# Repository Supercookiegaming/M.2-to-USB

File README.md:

# M.2-to-USB Adapter Card

## Overview
The M.2 to USB adapater uses the single USB 2.0 lane on the A/E Key M.2 slot to make an USB 2.0 front panel connector. The board uses the Microchip USB2422 2 port USB 2.0 hub chipset.
## Specifications
1. 500mA per port
2. Short circuit protection
3. 2 USB 2.0 ports (combined into standard internal PC header)
4. 2230 A & E Key compatibility
## Instructions

* [Ordering Instructions](Instructions/PCB_Order_Instructions.md)
* [KiCad Instructions](Instructions/KiCad_Install_Instructions.md)
* [Soldering Instructions](Instructions/Soldering_Instructions.md)

The board is free to use for personal use only.

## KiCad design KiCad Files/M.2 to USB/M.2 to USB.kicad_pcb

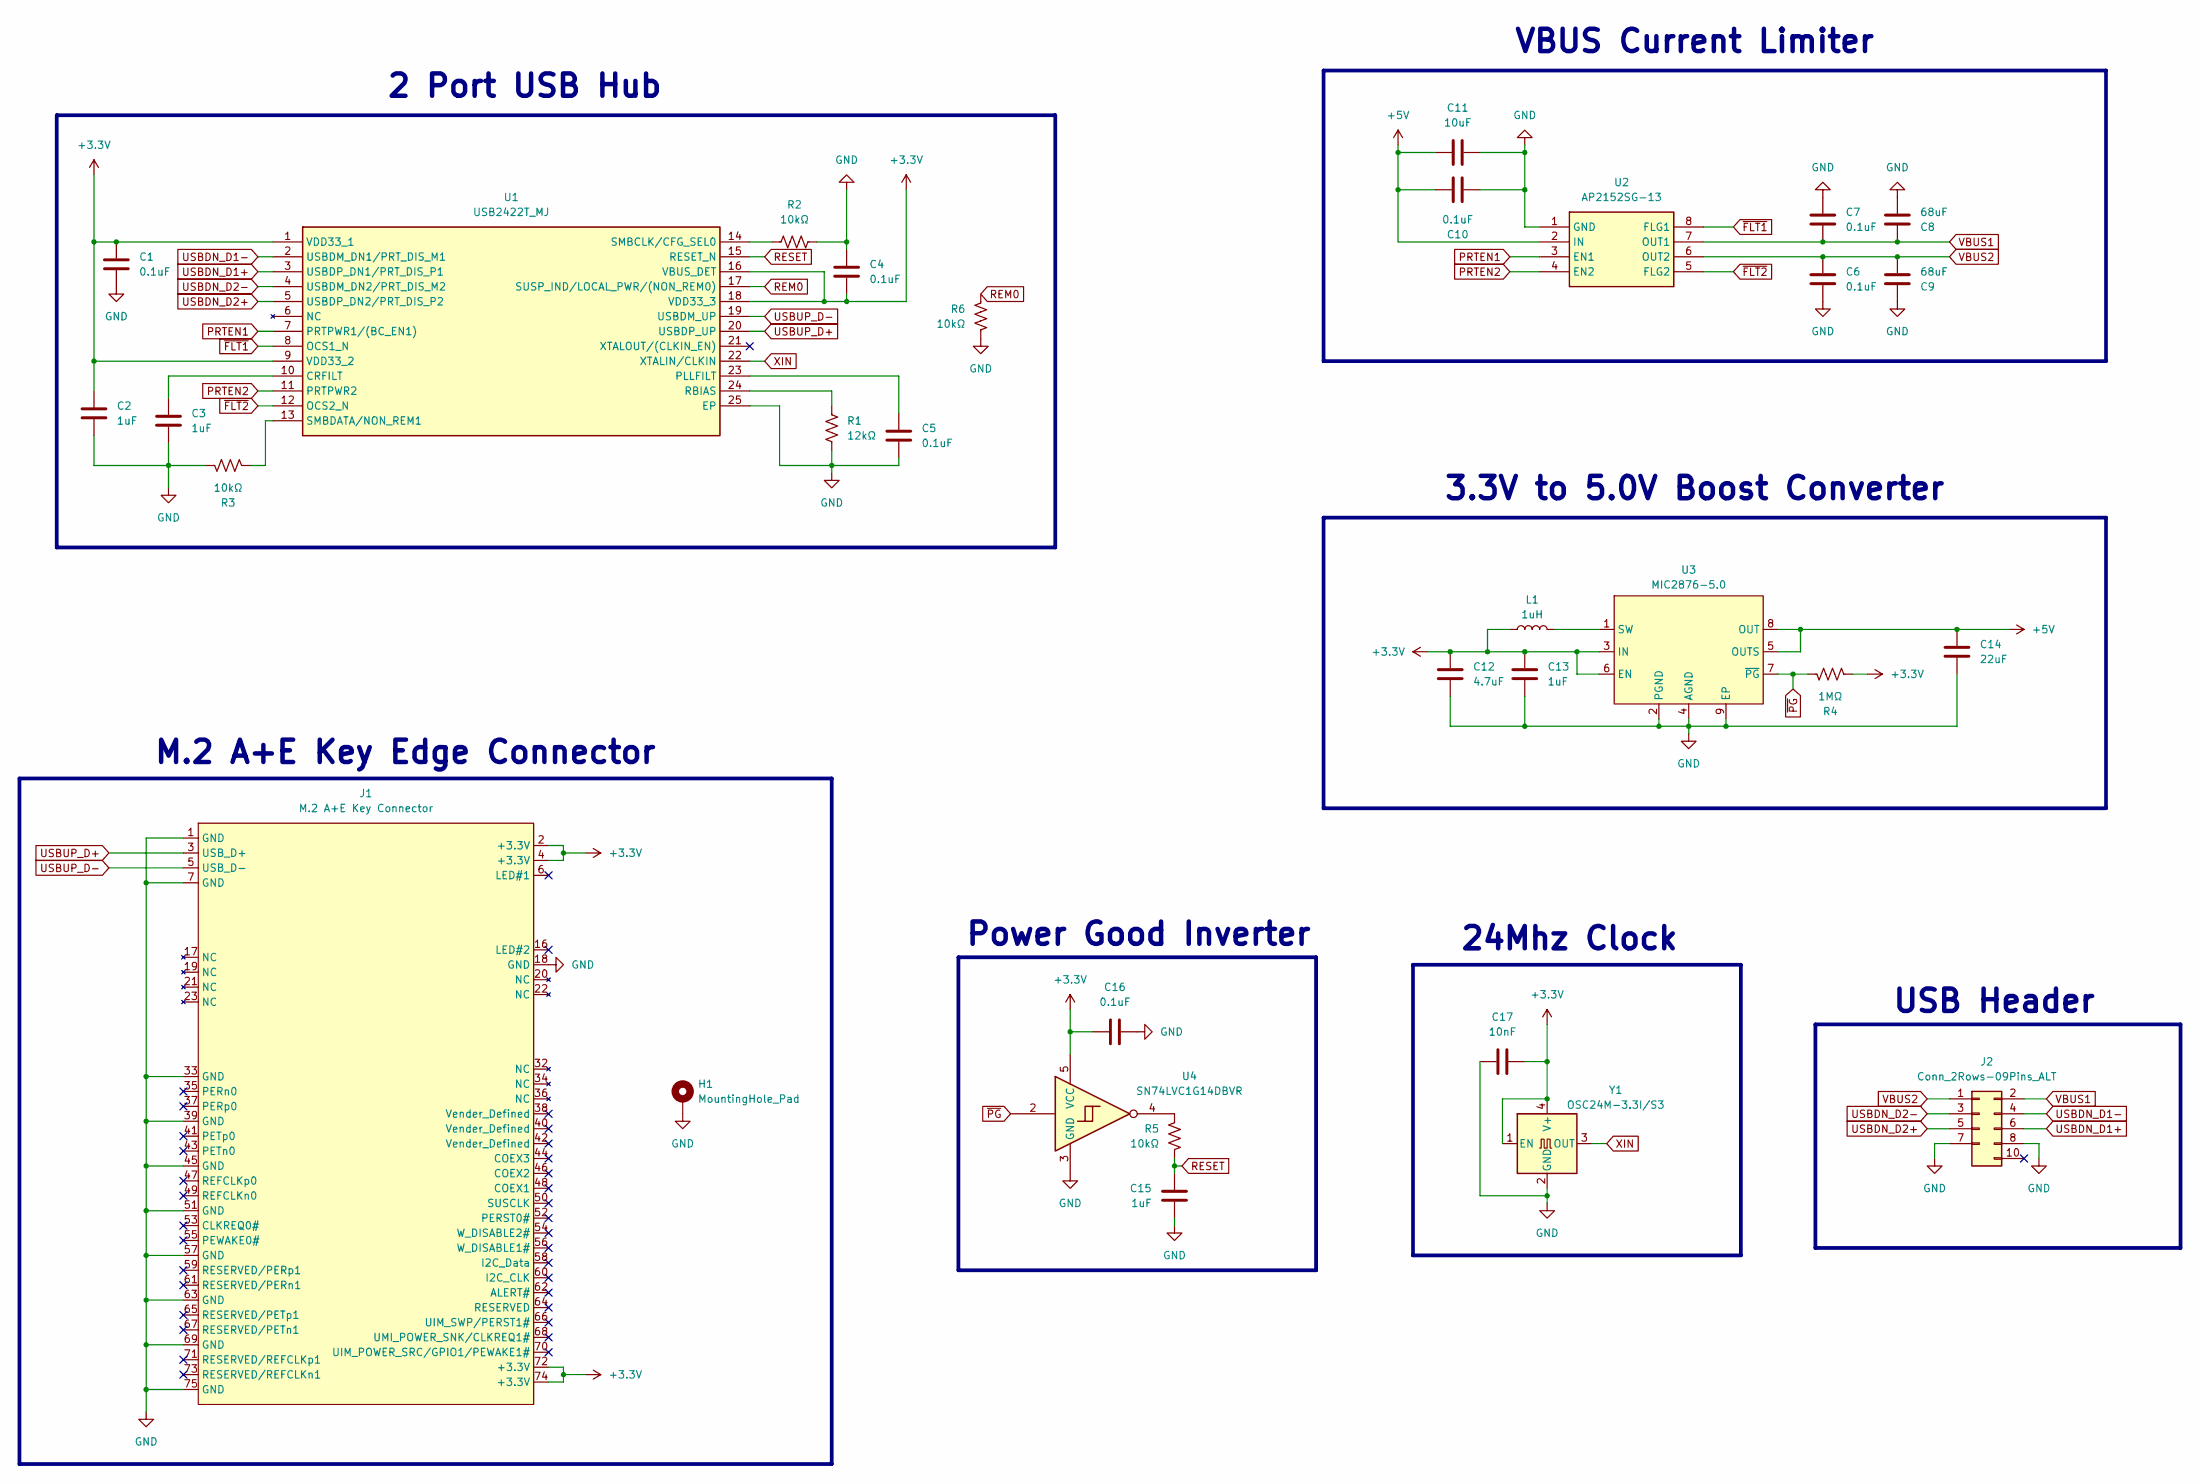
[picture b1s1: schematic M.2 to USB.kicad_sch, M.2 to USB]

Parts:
C1, C4, C5, C6, C7, C10, C16: 0.1uF; C_0402_1005Metric
C2, C3, C13, C15: 1uF; C_0402_1005Metric
C8, C9: 68uF; C_1206_3216Metric
C11: 10uF; C_0402_1005Metric
C12: 4.7uF; C_0402_1005Metric
C14: 22uF; C_0805_2012Metric
C17: 10nF; C_0402_1005Metric
H1: MountingHole_Pad; M.2 Mounting Pad
J1: M.2 A+E Key Connector
J2: Conn_2Rows-09Pins_ALT; PinHeader_2x05_P2.54mm_Vertical_KEY_9
L1: 1uH; L_2520_INPAQ
R1: 12kΩ; R_0402_1005Metric
R2, R3, R5, R6: 10kΩ; R_0402_1005Metric
R4: 1MΩ; R_0402_1005Metric
U1: USB2422T_MJ; QFN50P400X400X100-25N-D; Manufacturer_Part_Number USB2422T/MJ; Mouser Part Number 579-USB2422T/MJ
U2: AP2152SG-13; SOIC127P600X175-8N; Manufacturer_Part_Number AP2152SG-13; Mouser Part Number 621-AP2152SG-13
U3: MIC2876-5.0; 8-Lead UDFN
U4: SN74LVC1G14DBVR; SOT-23-5
Y1: OSC24M-3.3I/S3; 4-SMD-3.2-2.5

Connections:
+3.3V: C1.1, C2.1, C4.2, C12.1, C13.1, C16.1, C17.1, J1.2 (+3.3V), J1.4 (+3.3V), J1.72 (+3.3V), J1.74 (+3.3V), L1.1, R4.1, U1.1 (VDD33_1), U1.9 (VDD33_2), U1.16 (VBUS_DET), U1.18 (VDD33_3), U3.3 (IN), U3.6 (EN), U4.5 (VCC), Y1.1 (EN), Y1.4 (V+)
+5V: C10.1, C11.1, C14.1, U2.2 (IN), U3.5 (OUTS), U3.8 (OUT)
GND: C1.2, C2.2, C3.2, C4.1, C5.2, C6.2, C7.1, C8.2, C9.1, C10.2, C11.2, C12.2, C13.2, C14.2, C15.2, C16.2, C17.2, H1.1, J1.1 (GND), J1.7 (GND), J1.18 (GND), J1.33 (GND), J1.39 (GND), J1.45 (GND), J1.51 (GND), J1.57 (GND), J1.63 (GND), J1.69 (GND), J1.75 (GND), J2.7, J2.8, R1.2, R2.2, R3.2, R6.2, U1.25 (EP), U2.1 (GND), U3.2 (PGND), U3.4 (AGND), U3.9 (EP), U4.3 (GND), Y1.2 (GND)
unnamed: R5.1, U4.4
unnamed: C3.1, U1.10 (CRFILT)
unnamed: C5.1, U1.23 (PLLFILT)
unnamed: R1.1, U1.24 (RBIAS)
unnamed: R2.1, U1.14 (SMBCLK/CFG_SEL0)
unnamed: R3.1, U1.13 (SMBDATA/NON_REM1)
unnamed: L1.2, U3.1 (SW)
PRTEN1: U1.7 (PRTPWR1/(BC_EN1)), U2.3 (EN1)
PRTEN2: U1.11 (PRTPWR2), U2.4 (EN2)
REM0: R6.1, U1.17 (SUSP_IND/LOCAL_PWR/(NON_REM0))
RESET: C15.1, R5.2, U1.15 (RESET_N)
USBDN_D1+: J2.6, U1.3 (USBDP_DN1/PRT_DIS_P1)
USBDN_D1-: J2.4, U1.2 (USBDM_DN1/PRT_DIS_M1)
USBDN_D2+: J2.5, U1.5 (USBDP_DN2/PRT_DIS_P2)
USBDN_D2-: J2.3, U1.4 (USBDM_DN2/PRT_DIS_M2)
USBUP_D+: J1.3 (USB_D+), U1.20 (USBDP_UP)
USBUP_D-: J1.5 (USB_D-), U1.19 (USBDM_UP)
VBUS1: C7.2, C8.1, J2.2, U2.7 (OUT1)
VBUS2: C6.1, C9.2, J2.1, U2.6 (OUT2)
XIN: U1.22 (XTALIN/CLKIN), Y1.3 (OUT)
~FLT1: U1.8 (OCS1_N), U2.8 (FLG1)
~FLT2: U1.12 (OCS2_N), U2.5 (FLG2)
~PG: R4.2, U3.7 (~PG), U4.2

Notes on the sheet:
VBUS Current Limiter
2 Port USB Hub
M.2 A+E Key Edge Connector
Power Good Inverter
USB Header
3.3V to 5.0V Boost Converter
24Mhz Clock

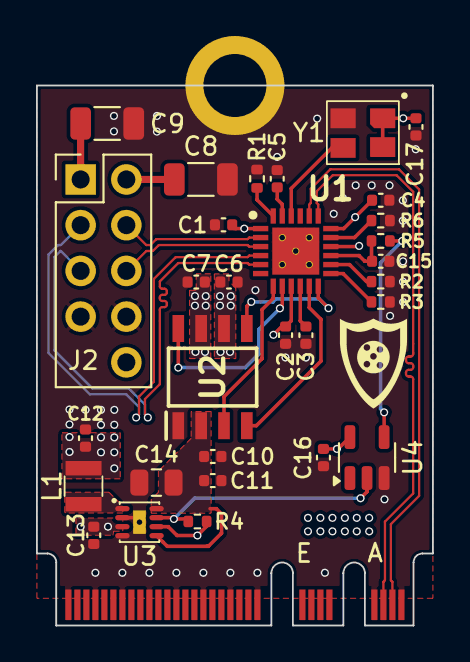
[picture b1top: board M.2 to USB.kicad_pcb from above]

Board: 4 copper layers, 22.0 x 30.0 mm, 32 parts (0 on the bottom side), 26 nets.

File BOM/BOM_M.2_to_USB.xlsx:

Board QTY | 1
Total Price | 8.0399999999999991
Board Designator | Part Number | Part Purpose | QTY per Board | Unit Price | QTY Needed | Total Price | Link
U1 | USB2422/MJ | USB Hub | 1 | 1.49 | 1 | 1.49 | https://www.digikey.com/en/products/detail/microchip-technol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
U2 | AP2152SG-13 | USB VBUS Current Limiter | 1 | 0.39 | 1 | 0.39 | https://www.digikey.com/en/products/detail/diodes-incorporat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
U3 | MIC2876-5.0YMT-TR | 5V Boost Converter | 1 | 0.62 | 1 | 0.62 | https://www.digikey.com/en/products/detail/microchip-technol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
U4 | SN74LVC1G14DBVR | PG Signal Inverter | 1 | 0.11 | 1 | 0.11 | https://www.digikey.com/en/products/detail/texas-instruments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
Y1 | OSC24M-3.3I/S3 | 24Mhz Clock Generator | 1 | 0.73 | 1 | 0.73 | https://www.digikey.com/en/products/detail/yic/OSC24M-3-3I-S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
J2 | HTSW-105-07-T-D-009 | Internal USB 2.0 Header | 1 | 0.96 | 1 | 0.96 | https://www.digikey.com/en/products/detail/samtec-inc/HTSW-1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
R1 | RC0402FR-0712KL | 12kΩ Bias Resistor | 1 | 0.1 | 1 | 0.1 | https://www.digikey.com/en/products/detail/yageo/RC0402FR-07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
R2, R3, R5, R6 | RC0402FR-0712KL | 10kΩ Pull Up/Down Resistor | 4 | 0.1 | 4 | 0.4 | https://www.digikey.com/en/products/detail/yageo/RC0402JR-07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
R4 | WR04X1004FTL | 1MΩ Power Good Pull Up Resistor | 1 | 0.1 | 1 | 0.1 | https://www.digikey.com/en/products/detail/walsin-technology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
C1, C4, C5, C6, C7, C10, C16 | CL05A104KP5NNNC | 0.1uF Decoupling Caps | 7 | 0.08 | 7 | 0.56000000000000005 | https://www.digikey.com/en/products/detail/samsung-electro-m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
C2, C3, C13, C15 | C0402C105K9PACTU | 1uF Decoupling Caps | 4 | 0.08 | 4 | 0.32 | https://www.digikey.com/en/products/detail/kemet/C0402C105K9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
C8, C9 | C3216X5R0J686M160AB | 68uF VBUS Bulk Capacitors | 2 | 0.89 | 2 | 1.78 | https://www.digikey.com/en/products/detail/tdk-corporation/C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
C11 | GRM155R61A106ME11D | 10uF Decoupling Cap | 1 | 0.08 | 1 | 0.08 | https://www.digikey.com/en/products/detail/murata-electronic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
C12 | CL05A475KQ5NRNC | 4.7uF Input Cap for Boost Regtulator | 1 | 0.08 | 1 | 0.08 | https://www.digikey.com/en/products/detail/samsung-electro-m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
C14 | CL21A226MQQNNNG | 22uF Output Cap for Boost Regulator | 1 | 0.12 | 1 | 0.12 | https://www.digikey.com/en/products/detail/samsung-electro-m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
C17 | 0402B103K6R3CT | 10nF Decoupling Cap for Clock Chip | 1 | 0.1 | 1 | 0.1 | https://www.digikey.com/en/products/detail/walsin-technology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
L1 | WIP252012S-1R0MLDG | 1uH Boost Converter Inductor | 1 | 0.1 | 1 | 0.1 | https://www.digikey.com/en/products/detail/inpaq-technology-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

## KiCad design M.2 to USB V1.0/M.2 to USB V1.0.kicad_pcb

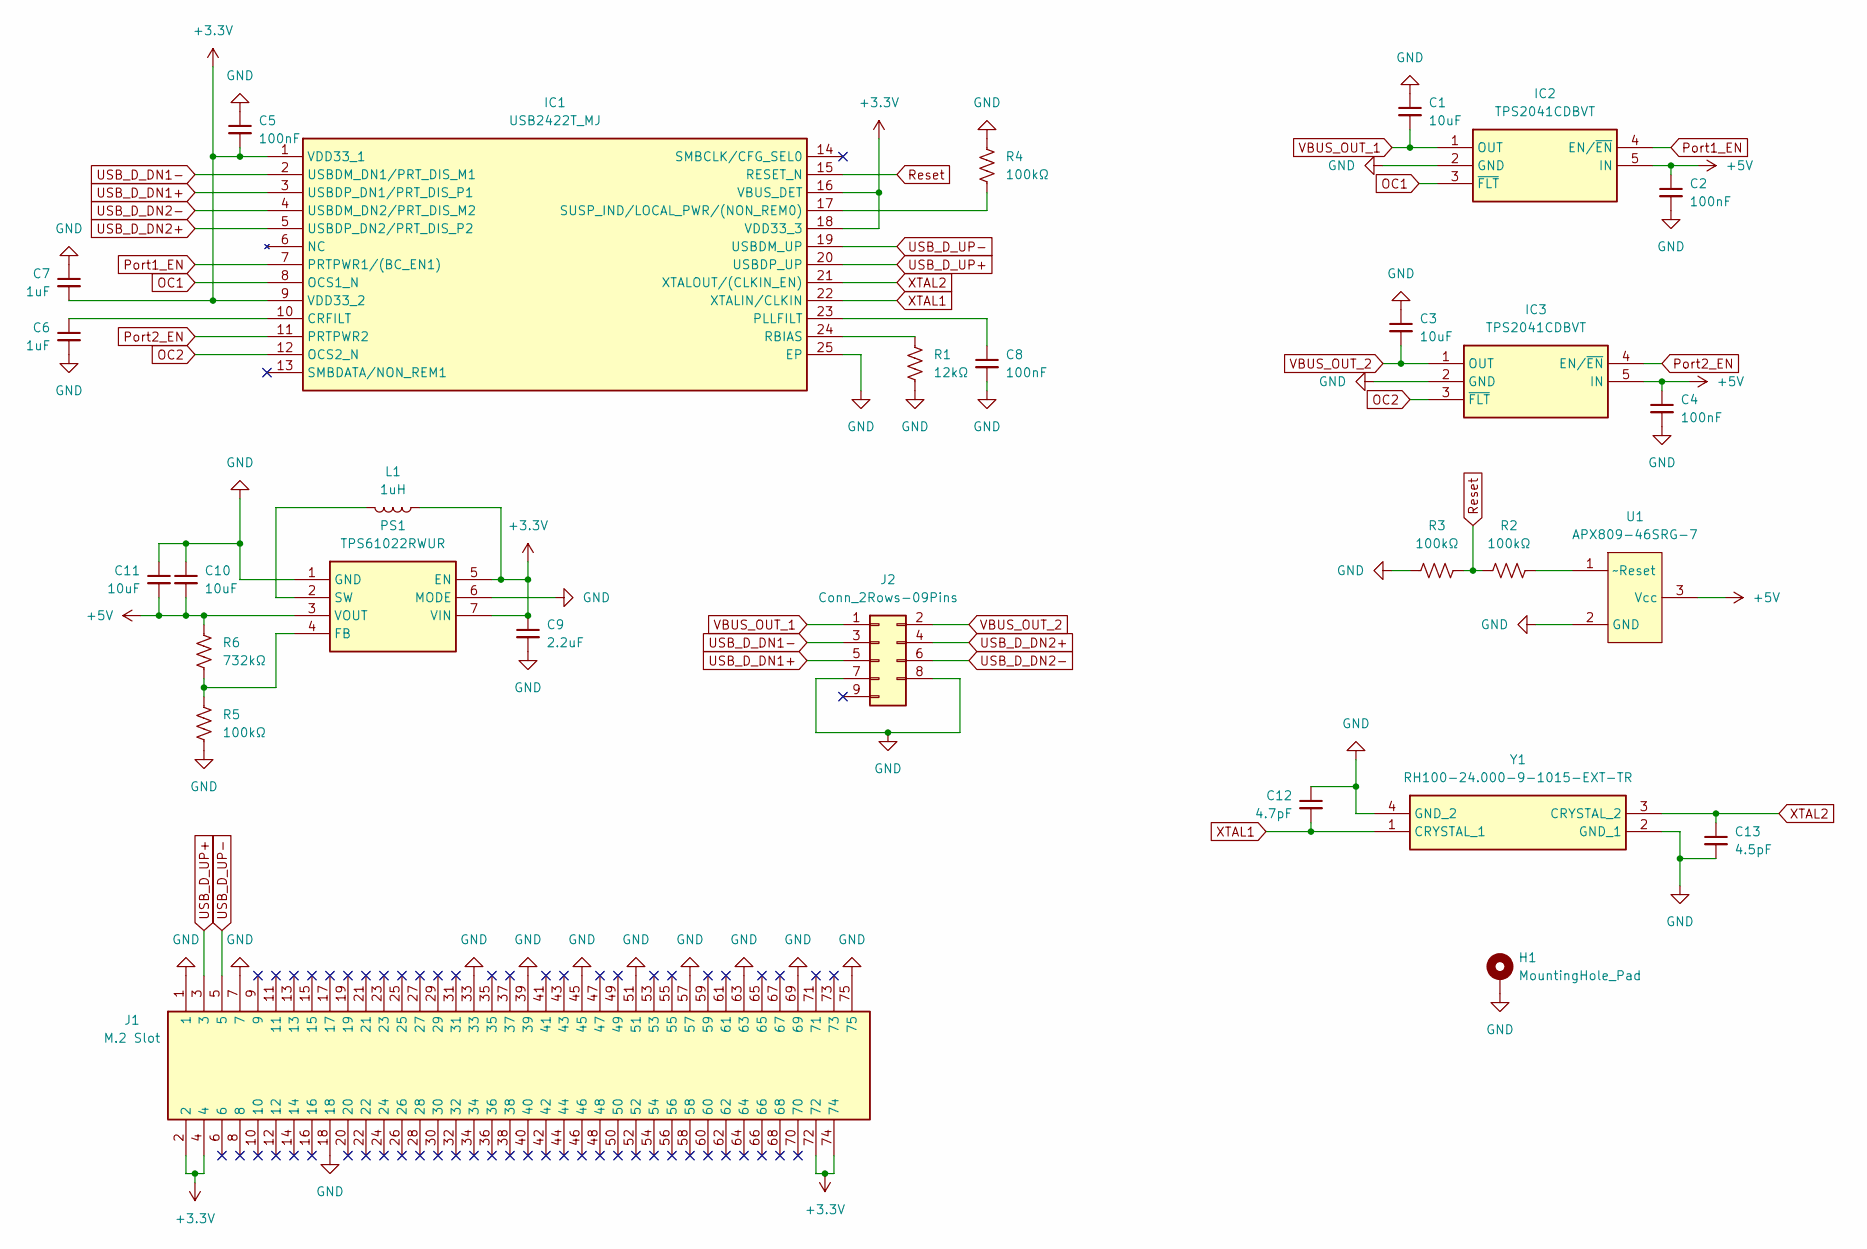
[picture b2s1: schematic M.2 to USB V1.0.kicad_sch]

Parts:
C1, C3, C10, C11: 10uF; C_0402_1005Metric_Pad0.74x0.62mm_HandSolder
C2, C4, C8: 100nF; C_0402_1005Metric_Pad0.74x0.62mm_HandSolder
C5: 100nF; C_0402_1005Metric
C6, C7: 1uF; C_0402_1005Metric_Pad0.74x0.62mm_HandSolder
C9: 2.2uF; C_0402_1005Metric_Pad0.74x0.62mm_HandSolder
C12: 4.7pF; C_0402_1005Metric_Pad0.74x0.62mm_HandSolder
C13: 4.5pF; C_0402_1005Metric_Pad0.74x0.62mm_HandSolder
H1: MountingHole_Pad; m.2 edge mount hole
IC1: USB2422T_MJ; QFN50P400X400X100-25N-D; Manufacturer_Part_Number USB2422T/MJ; Mouser Part Number 579-USB2422T/MJ
IC2, IC3: TPS2041CDBVT; SOT95P280X145-5N; Manufacturer_Part_Number TPS2041CDBVT; Mouser Part Number 595-TPS2041CDBVT
J1: M.2 Slot; NGFF_A+E; Manufacturer_Part_Number MDT420E03001; Mouser Part Number 523-MDT420E03001
J2: Conn_2Rows-09Pins; USB 2.0 Front Header
L1: 1uH; L_Bourns_SRN6045TA
PS1: TPS61022RWUR; Manufacturer_Part_Number TPS61022RWUR; Mouser Part Number 595-TPS61022RWUR
R1: 12kΩ; R_0402_1005Metric
R2, R3, R4, R5: 100kΩ; R_0402_1005Metric_Pad0.72x0.64mm_HandSolder
R6: 732kΩ; R_0402_1005Metric_Pad0.72x0.64mm_HandSolder
U1: APX809-46SRG-7; APX809-SR
Y1: RH100-24.000-9-1015-EXT-TR; RH10010000105050TR; Manufacturer_Part_Number RH100-24.000-9-1015-EXT-TR

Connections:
+3.3V: C5.2, C7.2, C9.1, IC1.1 (VDD33_1), IC1.9 (VDD33_2), IC1.16 (VBUS_DET), IC1.18 (VDD33_3), J1.2, J1.4, J1.72, J1.74, L1.1, PS1.5 (EN), PS1.7 (VIN)
+5V: C2.1, C4.1, C10.2, C11.2, IC2.5 (IN), IC3.5 (IN), PS1.3 (VOUT), R6.1, U1.3 (Vcc)
GND: C1.1, C2.2, C3.1, C4.2, C5.1, C6.2, C7.1, C8.2, C9.2, C10.1, C11.1, C12.1, C13.2, H1.1, IC1.25 (EP), IC2.2 (GND), IC3.2 (GND), J1.1, J1.7, J1.18, J1.33, J1.39, J1.45, J1.51, J1.57, J1.63, J1.69, J1.75, J2.7, J2.8, PS1.1 (GND), PS1.6 (MODE), R1.2, R3.2, R4.2, R5.2, U1.2 (GND), Y1.2 (GND_1), Y1.4 (GND_2)
unnamed: C6.1, IC1.10 (CRFILT)
unnamed: C8.1, IC1.23 (PLLFILT)
unnamed: IC1.24 (RBIAS), R1.1
unnamed: IC1.17 (SUSP_IND/LOCAL_PWR/(NON_REM0)), R4.1
unnamed: PS1.4 (FB), R5.1, R6.2
unnamed: L1.2, PS1.2 (SW)
unnamed: R2.1, U1.1 (~Reset)
OC1: IC1.8 (OCS1_N), IC2.3 (~FLT)
OC2: IC1.12 (OCS2_N), IC3.3 (~FLT)
Port1_EN: IC1.7 (PRTPWR1/(BC_EN1)), IC2.4 (EN/~EN)
Port2_EN: IC1.11 (PRTPWR2), IC3.4 (EN/~EN)
Reset: IC1.15 (RESET_N), R2.2, R3.1
USB_D_DN1+: IC1.3 (USBDP_DN1/PRT_DIS_P1), J2.5
USB_D_DN1-: IC1.2 (USBDM_DN1/PRT_DIS_M1), J2.3
USB_D_DN2+: IC1.5 (USBDP_DN2/PRT_DIS_P2), J2.4
USB_D_DN2-: IC1.4 (USBDM_DN2/PRT_DIS_M2), J2.6
USB_D_UP+: IC1.20 (USBDP_UP), J1.3
USB_D_UP-: IC1.19 (USBDM_UP), J1.5
VBUS_OUT_1: C1.2, IC2.1 (OUT), J2.1
VBUS_OUT_2: C3.2, IC3.1 (OUT), J2.2
XTAL1: C12.2, IC1.22 (XTALIN/CLKIN), Y1.1 (CRYSTAL_1)
XTAL2: C13.1, IC1.21 (XTALOUT/(CLKIN_EN)), Y1.3 (CRYSTAL_2)

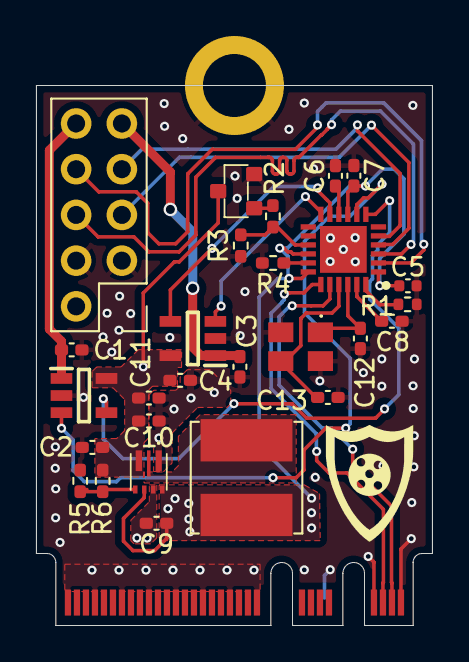
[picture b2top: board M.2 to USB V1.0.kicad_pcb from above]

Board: 2 copper layers, 22.0 x 30.0 mm, 29 parts (0 on the bottom side), 25 nets.

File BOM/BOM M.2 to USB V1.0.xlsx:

Board QTY | 1
Total Price | 9.6999999999999993
Board Designator | Part Number | Part Purpose | QTY per Board | Unit Price | QTY Needed | Total Price | Link
L1 | SRN6045TA-1R0Y | Boost Converter Inductor | 1 | 0.45 | 1 | 0.45 | https://www.digikey.com/en/products/detail/bourns-inc/SRN604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
U1 | APX809-46SRG-7 | Reset Signal Handler | 1 | 0.56999999999999995 | 1 | 0.56999999999999995 | https://www.digikey.com/en/products/detail/diodes-incorporat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
IC1 | USB2422T_MJ | USB 2.0 Hub | 1 | 1.58 | 1 | 1.58 | https://www.digikey.com/en/products/detail/microchip-technol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
IC2, IC3 | TPS2041CDBVT | USB Current Limiter | 2 | 1.1399999999999999 | 2 | 2.2799999999999998 | https://www.digikey.com/en/products/detail/texas-instruments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
PS1 | TPS61022RWUR | 3.3 to 5.0 Boost Converter | 1 | 1.67 | 1 | 1.67 | https://www.digikey.com/en/products/detail/texas-instruments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
R1 | ERA-2AEB123X | 12k Hub Bias Resistor | 1 | 0.1 | 1 | 0.1 | https://www.digikey.com/en/products/detail/panasonic-electro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
R2, R3, R4, R5 | ERJ-2RKF1003X | 100k pullup and divider Resistor | 4 | 0.1 | 4 | 0.4 | https://www.digikey.com/en/products/detail/panasonic-electro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
R6 | RC0402FR-07732KL | 732k Divider Resistor | 1 | 0.1 | 1 | 0.1 | https://www.digikey.com/en/products/detail/yageo/RC0402FR-07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
C1, C3, C10, C11 | CL05A106MP5NUNC | 10uF Filter Capacitor | 4 | 0.08 | 4 | 0.32 | https://www.digikey.com/en/products/detail/samsung-electro-m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
C2, C4, C5, C8 | CC0402JRX7R7BB104 | 100nF Filter Capacitor | 4 | 0.08 | 4 | 0.32 | https://www.digikey.com/en/products/detail/yageo/CC0402JRX7R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
C6, C7 | GRM155Z71A105KE01J | 1uF Filter Capacitor | 2 | 0.1 | 2 | 0.2 | https://www.digikey.com/en/products/detail/murata-electronic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
C9 | LMK105BJ225KV-F | 2.2uF Filter Cap | 1 | 0.1 | 1 | 0.1 | https://www.digikey.com/en/products/detail/taiyo-yuden/LMK10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
C12 | KGM05ACG1H4R7DH | 4.7pF Crystal Load Cap | 1 | 0.1 | 1 | 0.1 | https://www.digikey.com/en/products/detail/kyocera-avx/KGM05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
C13 | GJM1555C1H4R5WB01D | 4.5pF Crystal Load Cap | 1 | 0.14000000000000001 | 1 | 0.14000000000000001 | https://www.digikey.com/en/products/detail/murata-electronic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
J2 | TSW-105-07-G-D-010 | Front Panel USB 2.0 Header | 1 | 1.37 | 1 | 1.37 | https://www.digikey.com/en/products/detail/samtec-inc/TSW-10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

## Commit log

2025-04-17 Started Work on schematic
2025-04-17 updated schematic
2025-04-17 finished schematic
    finished schematic values of crystal caps not set. will be set after board design
2025-04-17 added all footprints
2025-04-17 finished pcb layout
2025-04-18 updated pcb
    updated pcb
    calculated load caps
    added 3D render
2025-04-18 updated pcb
2025-04-18 fixed copper pour bug
    bug caused by this (https://gitlab.com/kicad/code/kicad/-/issues?show=eyJpaWQiOiIyMDY5NiIsImZ1bGxfcGF0aCI6ImtpY2FkL2NvZGUva2ljYWQiLCJpZCI6MTY2MjEzNzM2fQ%3D%3D) caused copper pours to be corrupted. th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
2025-04-18 fixed missing ground connection
    pin 18 was not connected to ground net. it is now connected.
2025-04-18 Updated BOM
    added all parts to BOM
2025-04-18 Organized Schematic
2025-04-18 Organized files
2025-04-19 Added Gerber Files
2025-04-21 fixed error in BOM
2025-07-10 Updating File Structure
2025-08-02 first revision of v1.1 board version
    updated file and library structure
    -fixed issues #1 , #2 , #3 , #5 , #6 , #7
    -uses M.2 footprint from PCIexpress-KiCad
2025-08-02 added instruction files
2025-08-02 New Renders and updated board
    updated the footprints for usb2422, clock chip and m.2 connector.
    made new 2D and 3D renders of updated board.
2025-08-06 Updated v1.1 design
    -updated v1.1 design
    -finished schematic, pcb, render, gerber, and BOM
    -removed old v1.0 files
2025-08-06 fixed vbus nets
    vbus nets were corrected so flt/en port from the hub lined up with the usb port on the header
2025-08-07 optimized traces
    moved the header over a bit so second usb lane could be routed in a clean fashion
    made fill zones simpler
    remade gerber and renders
2025-08-07 updated schematic and testing new render file name
2025-08-07 updated file names to have relative link compatibility
    markdown relative links can't have spaces in them. spaces were removed from file and folder names and replaced them with underscores
2025-08-07 removed kicad temp files mentioned in gitignore
2026-06-16 added silkscreen version number to back
2026-06-16 updated gerber files for silkscreen change
    forgot to update the gerber in the last commit.
